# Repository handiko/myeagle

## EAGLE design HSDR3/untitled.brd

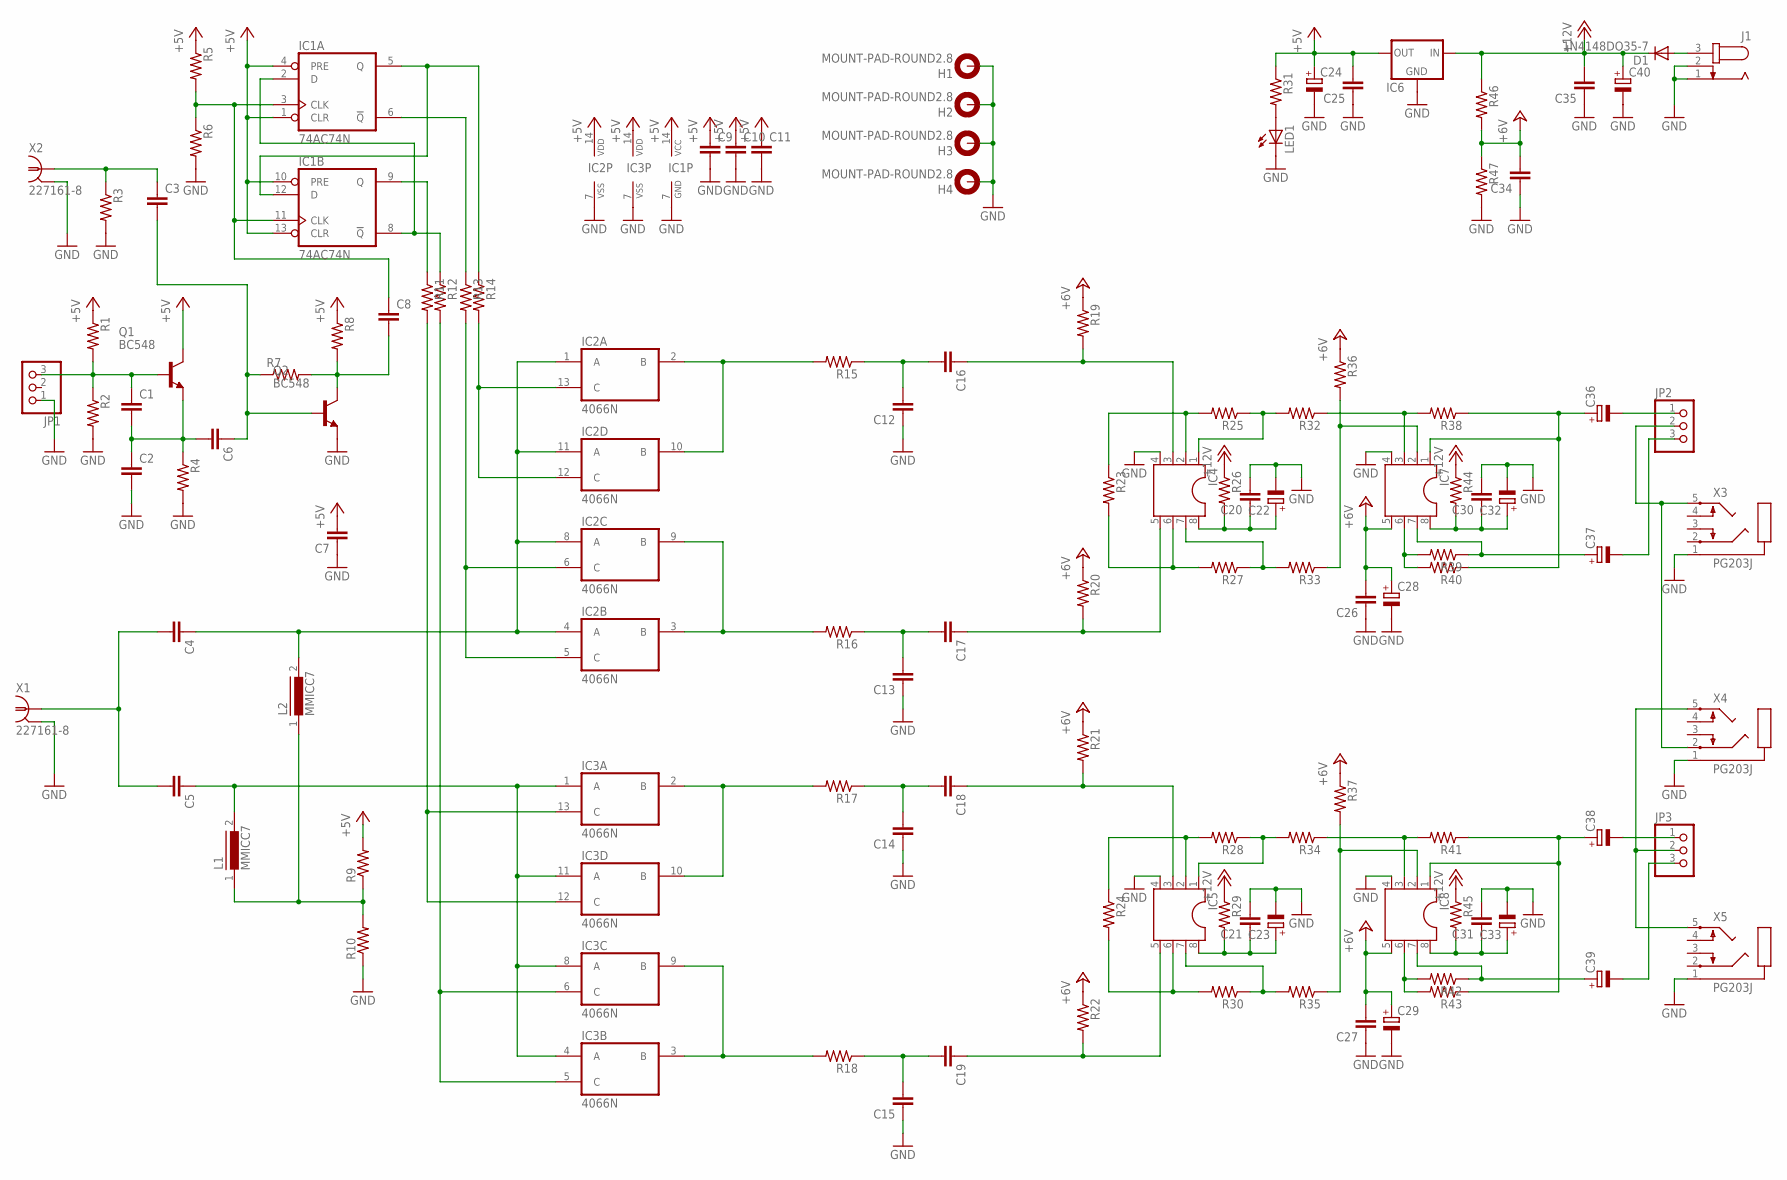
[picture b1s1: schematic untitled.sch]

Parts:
C1, C2: C-EU025-025X050; C025-025X050
C3, C4, C5, C6, C7, C9, C10, C11, C12, C13, C14, C15, C16, C17, C18, C19, C20, C21, C25, C26, C27, C30, C31, C34, C35: C-EU050-025X075; C050-025X075
C8: C-EU075-032X103; C075-032X103
C22, C23, C24, C28, C29, C32, C33, C36, C37, C38, C39, C40: CPOL-EUE5-6; E5-6
D1: 1N4148DO35-7; DO35-7
H1, H2, H3, H4: MOUNT-PAD-ROUND2.8; 2,8-PAD
IC1: 74AC74N; DIL14
IC2, IC3: 4066N; DIL14
IC4, IC5, IC7, IC8: DIL8; DIL08
IC6: 78XXS
J1: JACK-PLUG0; SPC4077
JP1, JP2, JP3: PINHD-1X3; 1X03
L1, L2: MMICC7
LED1: LED3MM
Q1, Q2: BC548; TO92-EBC
R1, R2, R3, R4, R5, R6, R7, R8, R9, R10, R11, R12, R13, R14, R15, R16, R17, R18, R19, R20, R21, R22, R23, R24, R25, R26, R27, R28, R29, R30, R31, R32, R33, R34, R35, R36, R37, R38, R39, R40, R41, R42, R43, R44, R45, R46, R47: R-US_0207/7; 0207/7
X1, X2: 227161-8; AMP_227161
X3, X4, X5: PG203J

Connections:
+5V: C7.2, C9.1, C10.1, C11.1, C24.+, C25.2, IC1.1 (CLR), IC1.4 (PRE), IC1.10 (PRE), IC1.13 (CLR), IC1.14 (VCC), IC2.14 (VDD), IC3.14 (VDD), IC6.OUT, Q1.C, R1.1, R5.1, R8.1, R9.2, R31.1
+12V: C35.2, C40.+, D1.C, IC6.IN, R26.1, R29.1, R44.1, R45.1, R46.1
+24V: C26.2, C27.2, C28.+, C29.+, C34.2, IC7.5, IC8.5, R19.1, R20.1, R21.1, R22.1, R36.1, R37.1, R46.2, R47.1
GND: C2.2, C7.1, C9.2, C10.2, C11.2, C12.1, C13.1, C14.1, C15.1, C20.2, C21.2, C22.-, C23.-, C24.-, C25.1, C26.1, C27.1, C28.-, C29.-, C30.2, C31.2, C32.-, C33.-, C34.1, C35.1, C40.-, H1.B2,8, H2.B2,8, H3.B2,8, H4.B2,8, IC1.7 (GND), IC2.7 (VSS), IC3.7 (VSS), IC4.4, IC5.4, IC6.GND, IC7.4, IC8.4, J1.1, J1.2, JP1.1, LED1.K (C), Q2.E, R2.2, R3.2, R4.2, R6.2, R10.1, R47.2, X1.2, X2.2, X3.1, X4.1, X5.1
unnamed: L1.1, L2.1, R9.1, R10.2
unnamed: C4.2, C5.2, X1.1
unnamed: C4.1, IC2.1 (A), IC2.4 (A), IC2.8 (A), IC2.11 (A), L2.2
unnamed: C5.1, IC3.1 (A), IC3.4 (A), IC3.8 (A), IC3.11 (A), L1.2
unnamed: IC2.3 (B), IC2.9 (B), R16.2
unnamed: IC2.2 (B), IC2.10 (B), R15.2
unnamed: IC3.2 (B), IC3.10 (B), R17.2
unnamed: IC3.3 (B), IC3.9 (B), R18.2
unnamed: IC2.12 (C), IC2.13 (C), R14.2
unnamed: IC2.5 (C), IC2.6 (C), R13.2
unnamed: IC3.12 (C), IC3.13 (C), R11.2
unnamed: IC3.5 (C), IC3.6 (C), R12.2
unnamed: C12.2, C16.2, R15.1
unnamed: C13.2, C17.2, R16.1
unnamed: C14.2, C18.2, R17.1
unnamed: C15.2, C19.2, R18.1
unnamed: IC1.2 (D), IC1.8 (!Q), R12.1
unnamed: IC1.6 (!Q), R13.1
unnamed: IC1.5 (Q), IC1.12 (D), R14.1
unnamed: IC1.9 (Q), R11.1
unnamed: C8.1, IC1.3 (CLK), IC1.11 (CLK), R5.2, R6.1
unnamed: C16.1, IC4.3, R19.2
unnamed: C17.1, IC4.5, R20.2
unnamed: IC4.2, R23.1, R25.2
unnamed: IC4.6, R23.2, R27.2
unnamed: IC4.7, R27.1, R33.2
unnamed: IC4.1, R25.1, R32.2
unnamed: IC7.2, R33.1, R36.2
unnamed: C36.+, IC7.1, R38.1, R40.1
unnamed: IC7.3, R32.1, R38.2
unnamed: IC7.6, R39.2, R40.2
unnamed: C37.+, IC7.7, R39.1
unnamed: C20.1, C22.+, IC4.8, R26.2
unnamed: C30.1, C32.+, IC7.8, R44.2
unnamed: D1.A, J1.3
unnamed: C3.1, R3.1, X2.1
unnamed: C36.-, JP2.1
unnamed: C18.1, IC5.3, R21.2
unnamed: C19.1, IC5.5, R22.2
unnamed: IC5.2, R24.1, R28.2
unnamed: IC5.6, R24.2, R30.2
unnamed: IC5.7, R30.1, R35.2
unnamed: IC5.1, R28.1, R34.2
unnamed: IC8.3, R34.1, R41.2
unnamed: IC8.2, R35.1, R37.2
unnamed: C38.+, IC8.1, R41.1, R43.1
unnamed: IC8.6, R42.2, R43.2
unnamed: C39.+, IC8.7, R42.1
unnamed: C21.1, C23.+, IC5.8, R29.2
unnamed: C31.1, C33.+, IC8.8, R45.2
unnamed: C37.-, JP2.3
unnamed: C38.-, JP3.1
unnamed: C39.-, JP3.3
unnamed: C1.1, JP1.3, Q1.B, R1.2, R2.1
unnamed: C1.2, C2.1, C6.2, Q1.E, R4.1
unnamed: JP2.2, X3.5, X4.2
unnamed: C8.2, Q2.C, R7.2, R8.2
unnamed: C3.2, C6.1, Q2.B, R7.1
unnamed: LED1.A, R31.2
unnamed: JP3.2, X4.5, X5.5

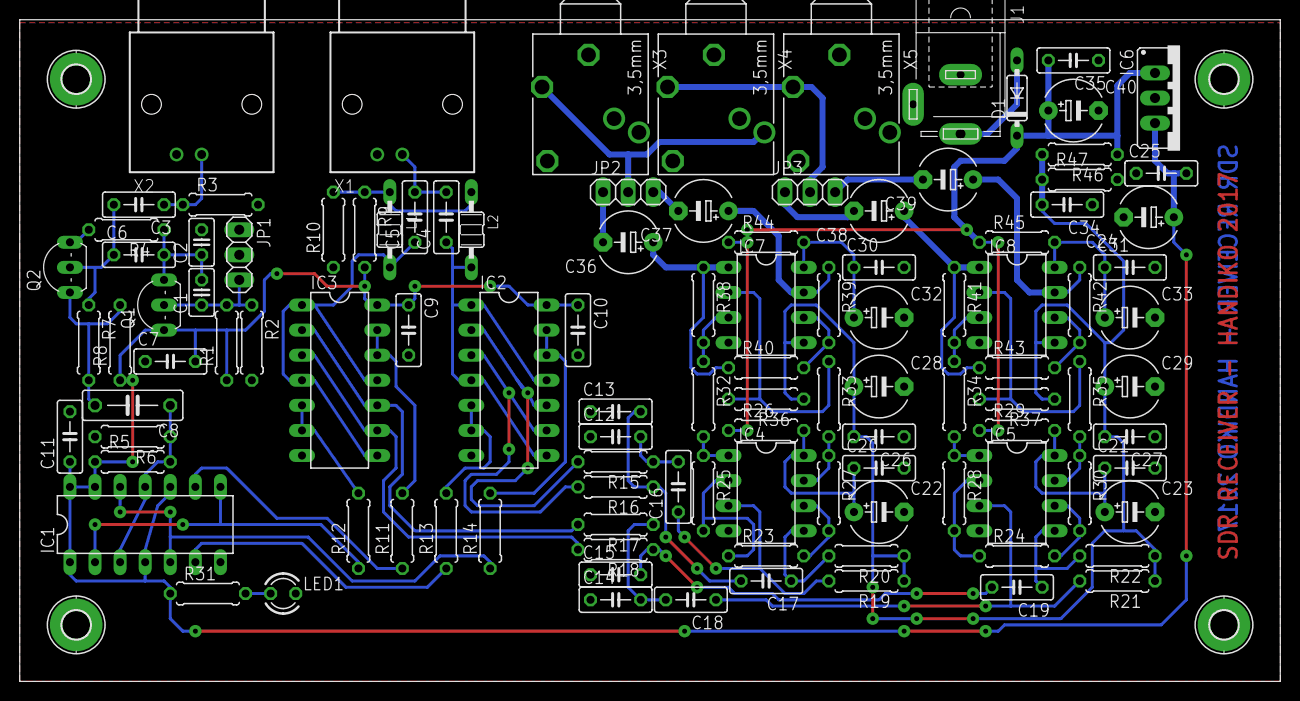
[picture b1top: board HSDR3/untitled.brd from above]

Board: 2 copper layers, 127.6 x 67.0 mm, 114 parts (0 on the bottom side), 64 nets.

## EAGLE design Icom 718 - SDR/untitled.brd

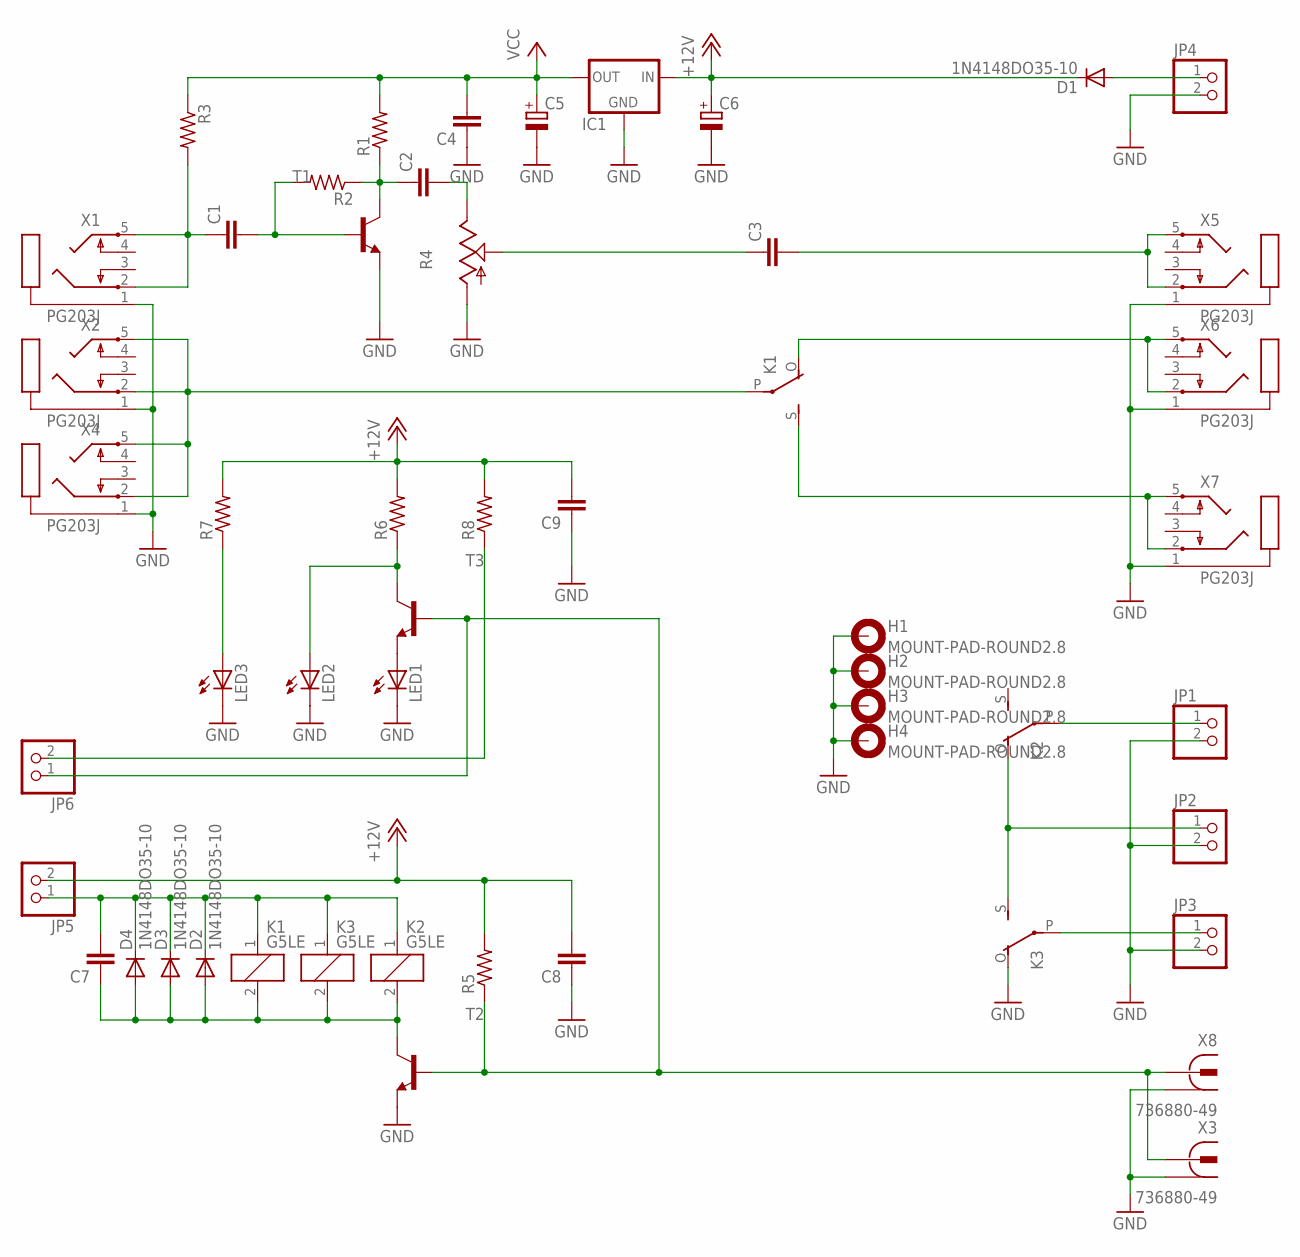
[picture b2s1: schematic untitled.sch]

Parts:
C1, C2, C3, C4, C7, C8, C9: C-EU050-025X075; C050-025X075
C5, C6: CPOL-EUE2.5-6; E2,5-6
D1, D2, D3, D4: 1N4148DO35-10; DO35-10
H1, H2, H3, H4: MOUNT-PAD-ROUND2.8; 2,8-PAD
IC1: 78XXS
JP1, JP2, JP3, JP4, JP5, JP6: PINHD-1X2; 1X02
K1, K2, K3: G5LE
LED1, LED2, LED3: LED3MM
R1, R2, R3, R5, R6, R7, R8: R-US_0207/7; 0207/7
R4: TRIM_US-CIP20C-6MM; CIP20C-6MM
T1, T2, T3: -NPN-TO92-EBC; TO92-EBC
X1, X2, X4, X5, X6, X7: PG203J
X3, X8: 736880-49

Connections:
+12V: C6.+, C8.2, C9.2, D1.C, IC1.IN, JP5.2, R5.2, R6.2, R7.2, R8.2
GND: C4.1, C5.-, C6.-, C8.1, C9.1, H1.B2,8, H2.B2,8, H3.B2,8, H4.B2,8, IC1.GND, JP1.2, JP2.2, JP3.2, JP4.2, K3.O, LED1.K (C), LED2.K (C), LED3.K (C), R4.A, T1.E, T2.E, X1.1, X2.1, X3.1, X3.1@1 (1), X3.1@2 (1), X4.1, X5.1, X6.1, X7.1, X8.1, X8.1@1 (1), X8.1@2 (1)
unnamed: C3.1, R4.S
unnamed: C1.1, R3.2, X1.2, X1.5
unnamed: C1.2, R2.2, T1.B
unnamed: C2.1, R1.1, R2.1, T1.C
unnamed: C2.2, R4.E
unnamed: JP6.1, R5.1, T2.B, T3.B, X3.2, X8.2
unnamed: C3.2, X5.2, X5.5
unnamed: K1.P, X2.2, X2.5, X4.2, X4.5
unnamed: K1.O, X6.2, X6.5
unnamed: K1.S, X7.2, X7.5
unnamed: JP3.1, K3.P
unnamed: JP1.1, K2.P
unnamed: JP2.1, K2.O, K3.S
unnamed: D1.A, JP4.1
unnamed: C7.1, D2.A, D3.A, D4.A, K1.2, K2.2, K3.2, T2.C
unnamed: JP6.2, R8.1
unnamed: C7.2, D2.C, D3.C, D4.C, JP5.1, K1.1, K2.1, K3.1
unnamed: LED1.A, T3.E
unnamed: LED2.A, R6.1, T3.C
unnamed: LED3.A, R7.1
VCC: C4.2, C5.+, IC1.OUT, R1.2, R3.1

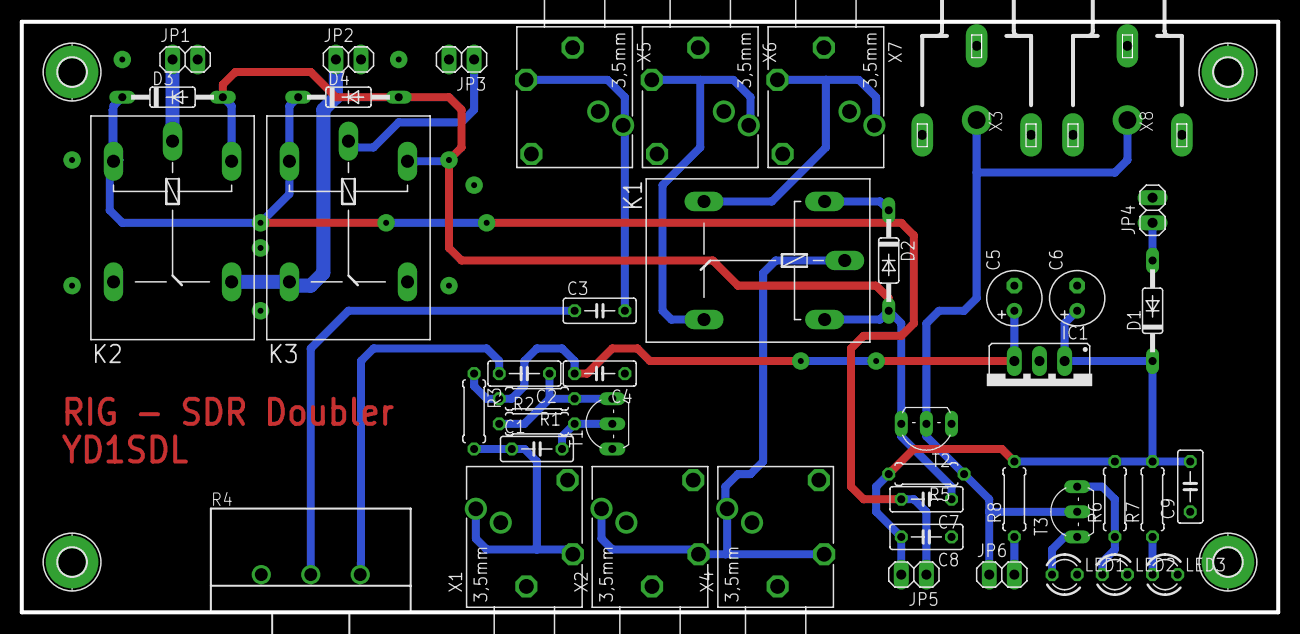
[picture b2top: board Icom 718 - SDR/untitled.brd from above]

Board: 2 copper layers, 127.0 x 59.7 mm, 49 parts (0 on the bottom side), 23 nets.

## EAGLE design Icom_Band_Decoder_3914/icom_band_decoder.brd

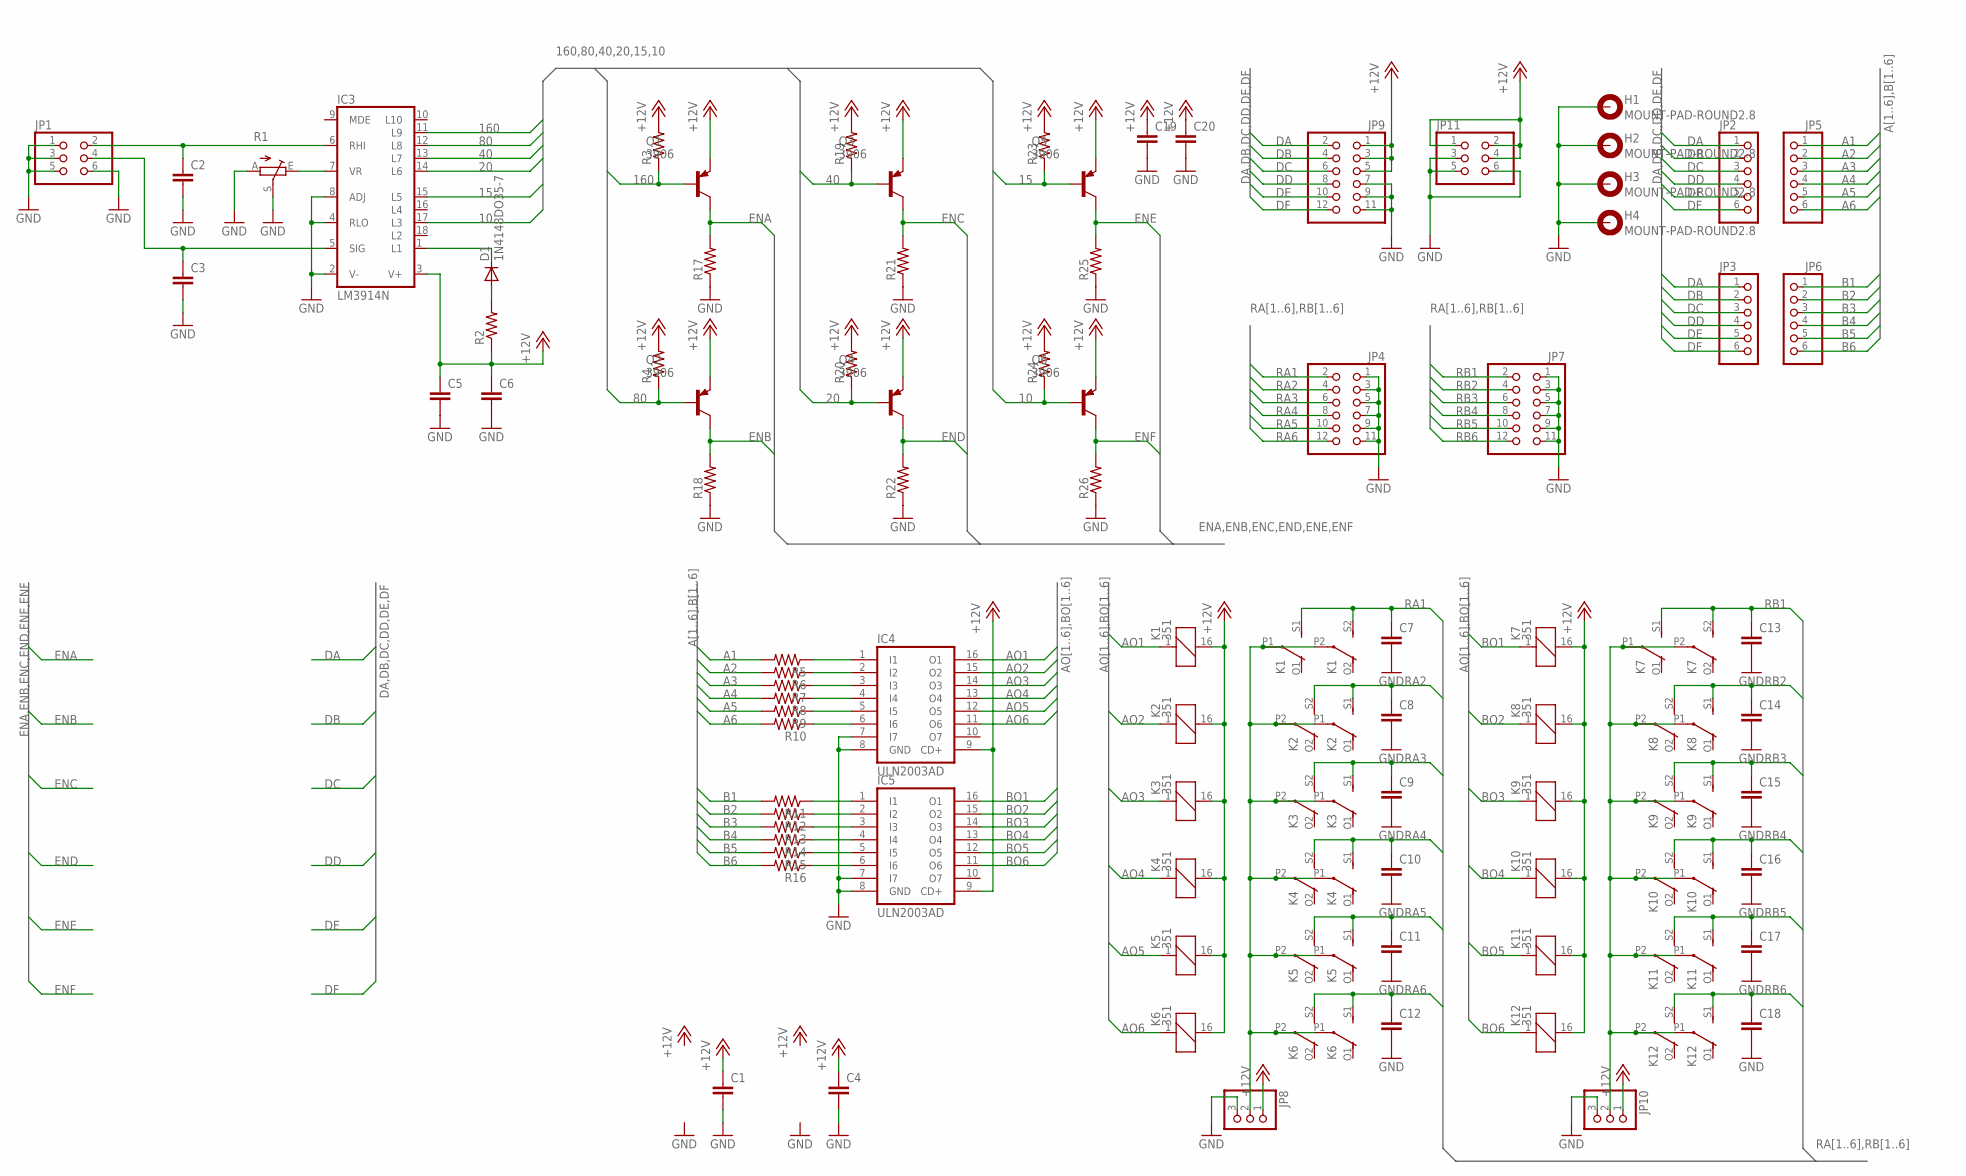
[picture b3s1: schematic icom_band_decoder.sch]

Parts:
C1, C4, C6, C7, C8, C9, C10, C11, C12, C13, C14, C15, C16, C17, C18, C19, C20: C-EU050-024X044; C050-024X044
C2, C3, C5: C-EUC0805K; C0805K
D1: 1N4148DO35-7; DO35-7
H1, H2, H3, H4: MOUNT-PAD-ROUND2.8; 2,8-PAD
IC3: LM3914N; DIL18
IC4, IC5: ULN2003AD; SO16
JP1, JP11: PINHD-2X3; 2X03
JP2, JP3, JP5, JP6: PINHD-1X6; 1X06
JP4, JP7, JP9: PINHD-2X6; 2X06
JP8, JP10: PINHD-1X3; 1X03
K1, K2, K3, K4, K5, K6, K7, K8, K9, K10, K11, K12: 351
Q1, Q2, Q3, Q4, Q5, Q6: 3906; SOT23-BEC
R1: TRIM_EU-CA6V; CA6V
R2, R3, R4, R5, R6, R7, R8, R9, R10, R11, R12, R13, R14, R15, R16, R17, R18, R19, R20, R21, R22, R23, R24, R25, R26: R-US_M0805; M0805

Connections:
10: IC3.17 (L3), Q6.B, R24.1
15: IC3.15 (L5), Q5.B, R23.1
20: IC3.14 (L6), Q4.B, R20.1
40: IC3.13 (L7), Q3.B, R19.1
80: IC3.12 (L8), Q2.B, R4.1
160: IC3.11 (L9), Q1.B, R3.1
+12V: C1.1, C4.1, C5.1, C6.1, C19.1, C20.1, IC3.3 (V+), IC4.9 (CD+), IC5.9 (CD+), JP8.1, JP9.1, JP9.3, JP9.5, JP10.1, JP11.1, JP11.2, JP11.4, K1.16 (2), K2.16 (2), K3.16 (2), K4.16 (2), K5.16 (2), K6.16 (2), K7.16 (2), K8.16 (2), K9.16 (2), K10.16 (2), K11.16 (2), K12.16 (2), Q1.E, Q2.E, Q3.E, Q4.E, Q5.E, Q6.E, R2.1, R3.2, R4.2, R19.2, R20.2, R23.2, R24.2
A1: JP5.1, R5.2
A2: JP5.2, R6.2
A3: JP5.3, R7.2
A4: JP5.4, R8.2
A5: JP5.5, R9.2
A6: JP5.6, R10.2
AO1: IC4.16 (O1), K1.1
AO2: IC4.15 (O2), K2.1
AO3: IC4.14 (O3), K3.1
AO4: IC4.13 (O4), K4.1
AO5: IC4.12 (O5), K5.1
AO6: IC4.11 (O6), K6.1
B1: JP6.1, R11.2
B2: JP6.2, R12.2
B3: JP6.3, R13.2
B4: JP6.4, R14.2
B5: JP6.5, R15.2
B6: JP6.6, R16.2
BO1: IC5.16 (O1), K7.1
BO2: IC5.15 (O2), K8.1
BO3: IC5.14 (O3), K9.1
BO4: IC5.13 (O4), K10.1
BO5: IC5.12 (O5), K11.1
BO6: IC5.11 (O6), K12.1
DA: JP2.1, JP3.1, JP9.2
DB: JP2.2, JP3.2, JP9.4
DC: JP2.3, JP3.3, JP9.6
DD: JP2.4, JP3.4, JP9.8
DE: JP2.5, JP3.5, JP9.10
DF: JP2.6, JP3.6, JP9.12
ENA: Q1.C, R17.2
ENB: Q2.C, R18.2
ENC: Q3.C, R21.2
END: Q4.C, R22.2
ENE: Q5.C, R25.2
ENF: Q6.C, R26.2
GND: C1.2, C2.2, C3.2, C4.2, C5.2, C6.2, C7.2, C8.2, C9.2, C10.2, C11.2, C12.2, C13.2, C14.2, C15.2, C16.2, C17.2, C18.2, C19.2, C20.2, H1.B2,8, H2.B2,8, H3.B2,8, H4.B2,8, IC3.2 (V-), IC3.4 (RLO), IC3.8 (ADJ), IC4.7 (I7), IC4.8 (GND), IC5.7 (I7), IC5.8 (GND), JP1.1, JP1.3, JP1.5, JP1.6, JP4.1, JP4.3, JP4.5, JP4.7, JP4.9, JP4.11, JP7.1, JP7.3, JP7.5, JP7.7, JP7.9, JP7.11, JP8.3, JP9.7, JP9.9, JP9.11, JP10.3, JP11.3, JP11.5, JP11.6, R1.A, R1.S, R17.1, R18.1, R21.1, R22.1, R25.1, R26.1
unnamed: C2.1, IC3.6 (RHI), JP1.2
unnamed: C3.1, IC3.5 (SIG), JP1.4
unnamed: IC3.7 (VR), R1.E
unnamed: D1.C, IC3.1 (L1)
unnamed: D1.A, R2.2
unnamed: IC4.1 (I1), R5.1
unnamed: IC4.2 (I2), R6.1
unnamed: IC4.3 (I3), R7.1
unnamed: IC4.4 (I4), R8.1
unnamed: IC4.5 (I5), R9.1
unnamed: IC4.6 (I6), R10.1
unnamed: IC5.1 (I1), R11.1
unnamed: JP8.2, K1.P1, K1.P2, K2.P1, K2.P2, K3.P1, K3.P2, K4.P1, K4.P2, K5.P1, K5.P2, K6.P1, K6.P2
unnamed: IC5.2 (I2), R12.1
unnamed: IC5.3 (I3), R13.1
unnamed: IC5.4 (I4), R14.1
unnamed: IC5.5 (I5), R15.1
unnamed: IC5.6 (I6), R16.1
unnamed: JP10.2, K7.P1, K7.P2, K8.P1, K8.P2, K9.P1, K9.P2, K10.P1, K10.P2, K11.P1, K11.P2, K12.P1, K12.P2
RA1: C7.1, JP4.2, K1.S1 (S), K1.S2 (S)
RA2: C8.1, JP4.4, K2.S1 (S), K2.S2 (S)
RA3: C9.1, JP4.6, K3.S1 (S), K3.S2 (S)
RA4: C10.1, JP4.8, K4.S1 (S), K4.S2 (S)
RA5: C11.1, JP4.10, K5.S1 (S), K5.S2 (S)
RA6: C12.1, JP4.12, K6.S1 (S), K6.S2 (S)
RB1: C13.1, JP7.2, K7.S1 (S), K7.S2 (S)
RB2: C14.1, JP7.4, K8.S1 (S), K8.S2 (S)
RB3: C15.1, JP7.6, K9.S1 (S), K9.S2 (S)
RB4: C16.1, JP7.8, K10.S1 (S), K10.S2 (S)
RB5: C17.1, JP7.10, K11.S1 (S), K11.S2 (S)
RB6: C18.1, JP7.12, K12.S1 (S), K12.S2 (S)

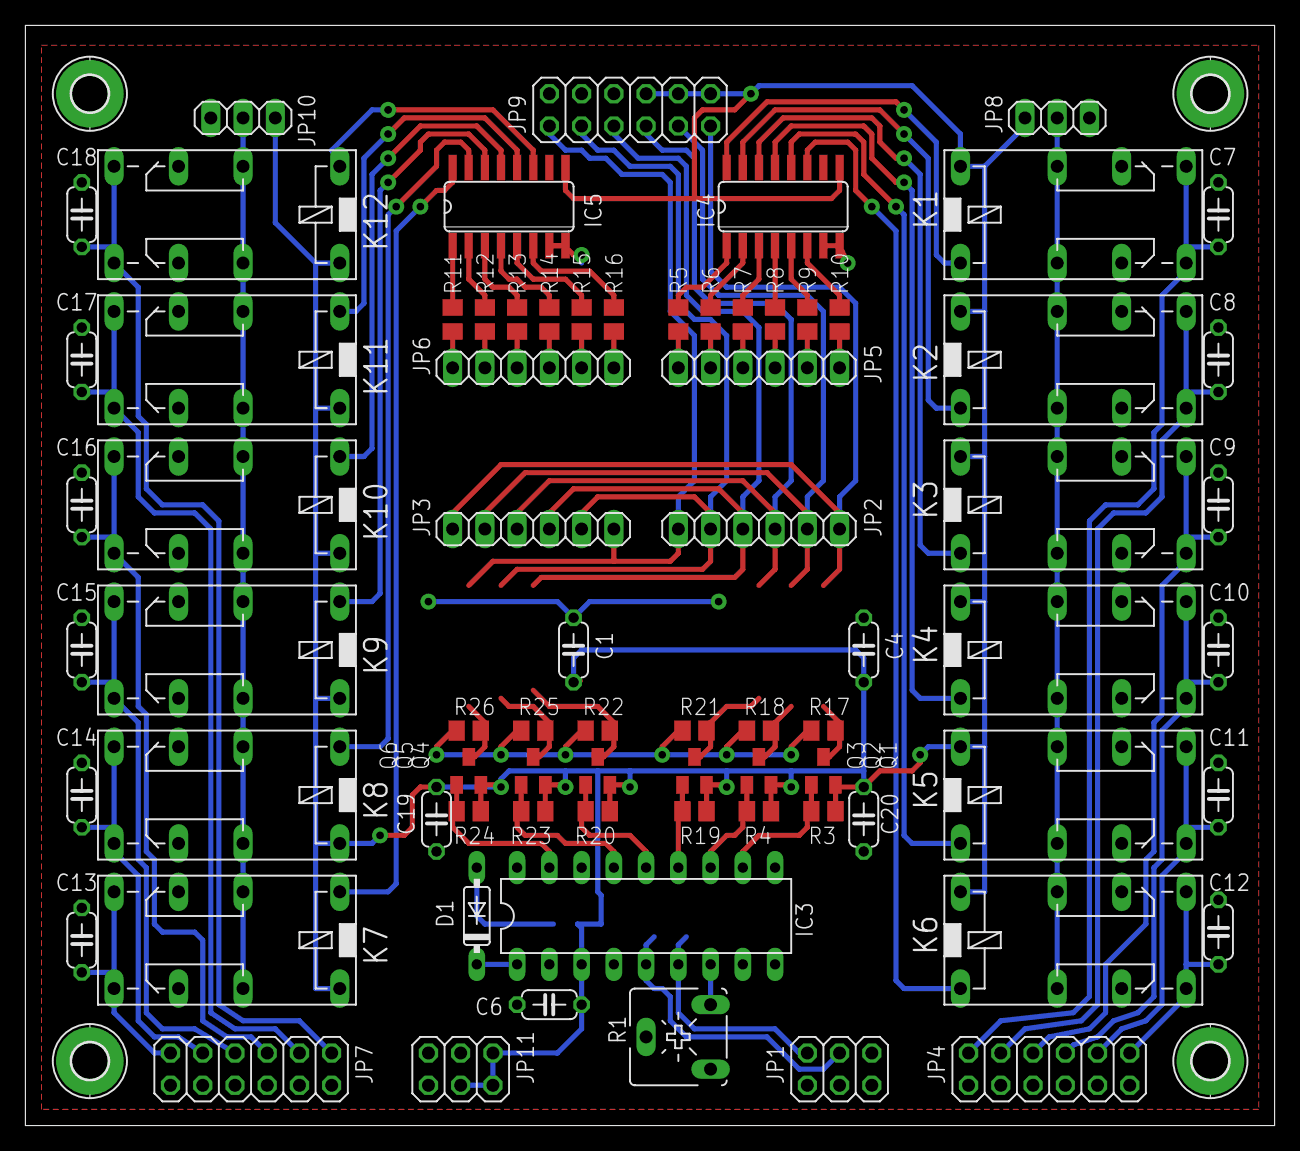
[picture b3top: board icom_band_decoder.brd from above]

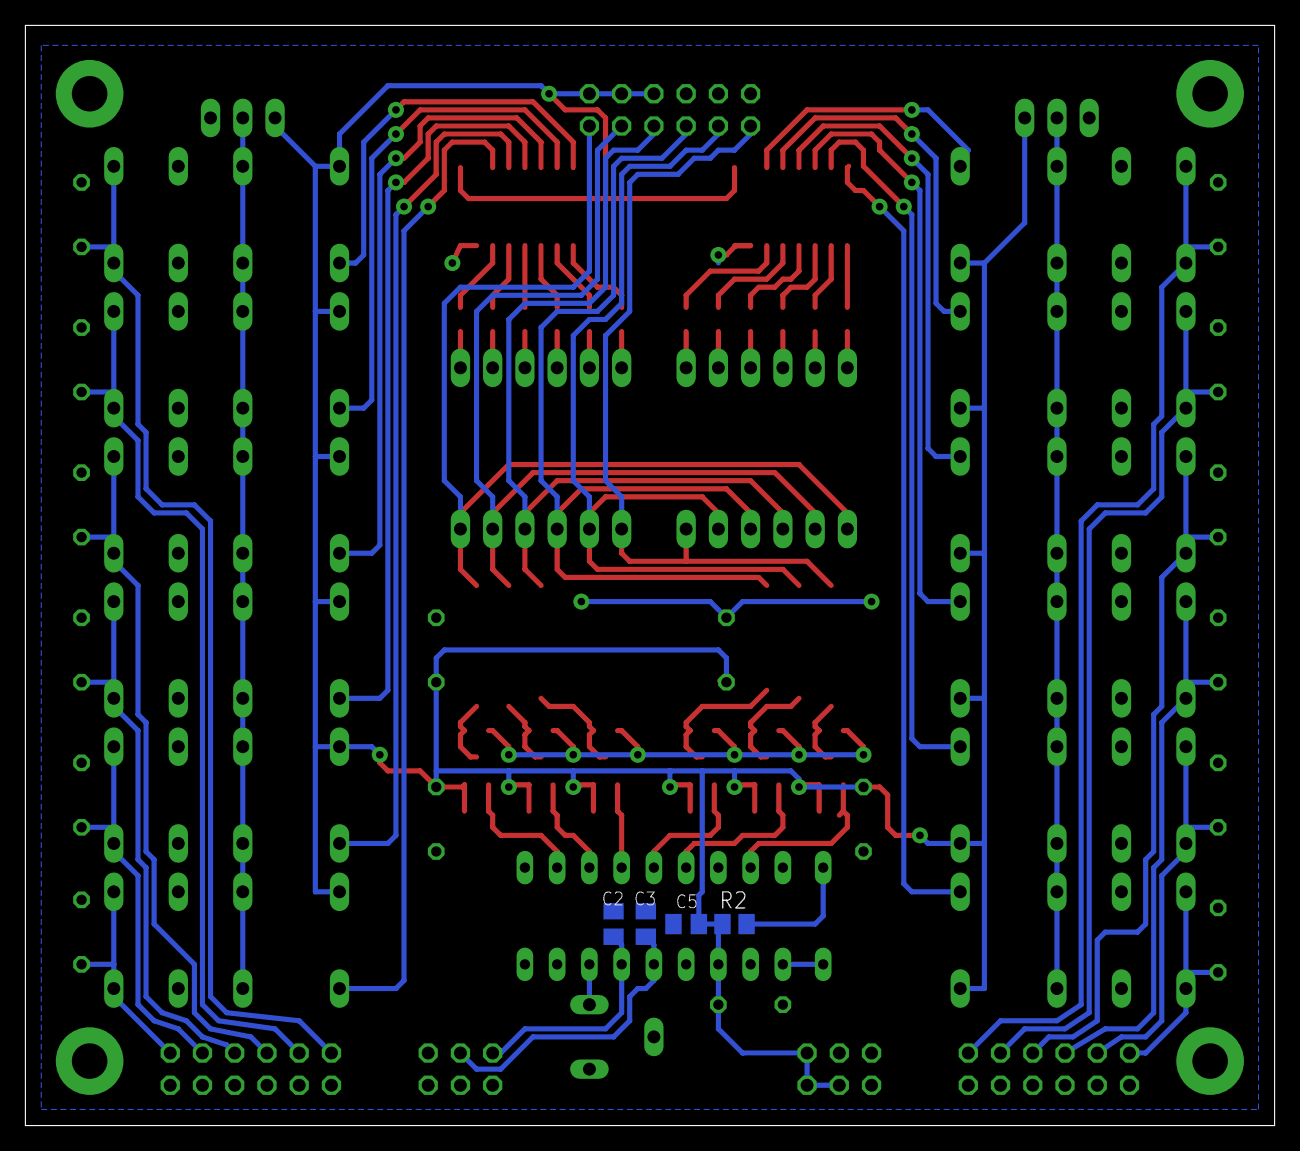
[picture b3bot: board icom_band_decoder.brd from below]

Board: 2 copper layers, 98.4 x 86.7 mm, 83 parts (4 on the bottom side), 75 nets.

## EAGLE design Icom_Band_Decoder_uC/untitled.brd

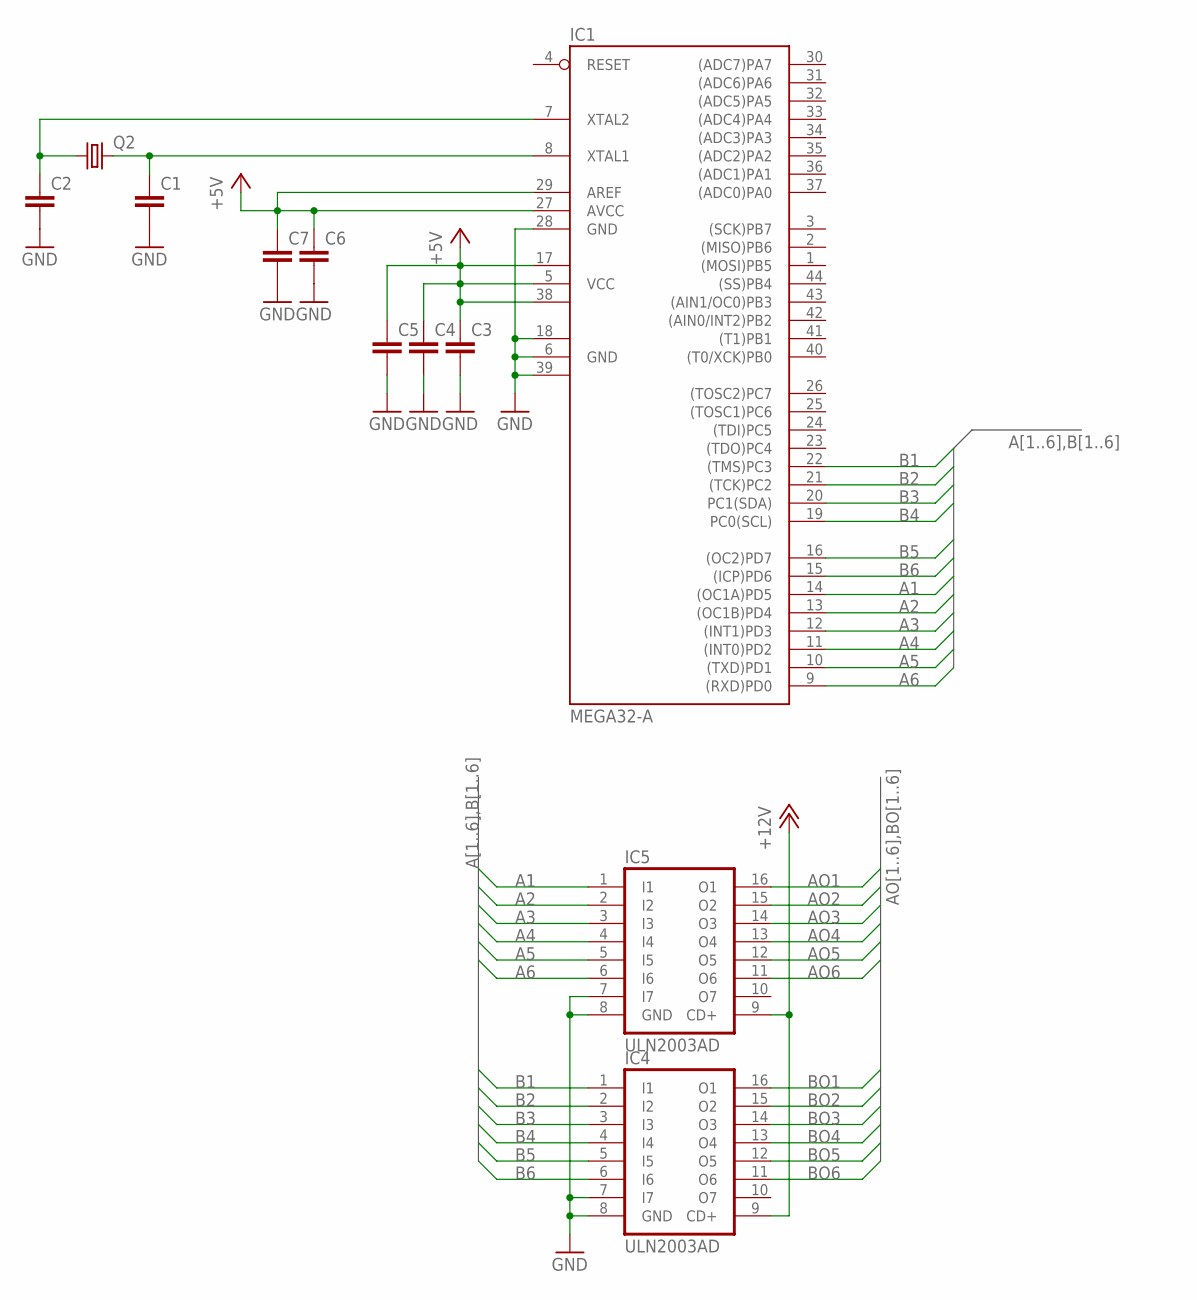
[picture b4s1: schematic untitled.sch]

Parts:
C1, C2, C3, C4, C5, C6, C7: C-EUC0805K; C0805K
IC1: MEGA32-A; TQFP44
IC4, IC5: ULN2003AD; SO16
Q2: CRYSTALSM49; SM49

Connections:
+5V: C3.1, C4.1, C5.1, C6.1, C7.1, IC1.5 (VCC), IC1.17 (VCC1), IC1.27 (AVCC), IC1.29 (AREF), IC1.38 (VCC2)
+12V: IC4.9 (CD+), IC5.9 (CD+)
A1: IC1.14 ((OC1A)PD5), IC5.1 (I1)
A2: IC1.13 ((OC1B)PD4), IC5.2 (I2)
A3: IC1.12 ((INT1)PD3), IC5.3 (I3)
A4: IC1.11 ((INT0)PD2), IC5.4 (I4)
A5: IC1.10 ((TXD)PD1), IC5.5 (I5)
A6: IC1.9 ((RXD)PD0), IC5.6 (I6)
AO1: IC5.16 (O1)
AO2: IC5.15 (O2)
AO3: IC5.14 (O3)
AO4: IC5.13 (O4)
AO5: IC5.12 (O5)
AO6: IC5.11 (O6)
B1: IC1.22 ((TMS)PC3), IC4.1 (I1)
B2: IC1.21 ((TCK)PC2), IC4.2 (I2)
B3: IC1.20 (PC1(SDA)), IC4.3 (I3)
B4: IC1.19 (PC0(SCL)), IC4.4 (I4)
B5: IC1.16 ((OC2)PD7), IC4.5 (I5)
B6: IC1.15 ((ICP)PD6), IC4.6 (I6)
BO1: IC4.16 (O1)
BO2: IC4.15 (O2)
BO3: IC4.14 (O3)
BO4: IC4.13 (O4)
BO5: IC4.12 (O5)
BO6: IC4.11 (O6)
GND: C1.2, C2.2, C3.2, C4.2, C5.2, C6.2, C7.2, IC1.6 (GND), IC1.18 (GND1), IC1.28 (GND), IC1.39 (GND2), IC4.7 (I7), IC4.8 (GND), IC5.7 (I7), IC5.8 (GND)
unnamed: C2.1, IC1.7 (XTAL2), Q2.1
unnamed: C1.1, IC1.8 (XTAL1), Q2.2

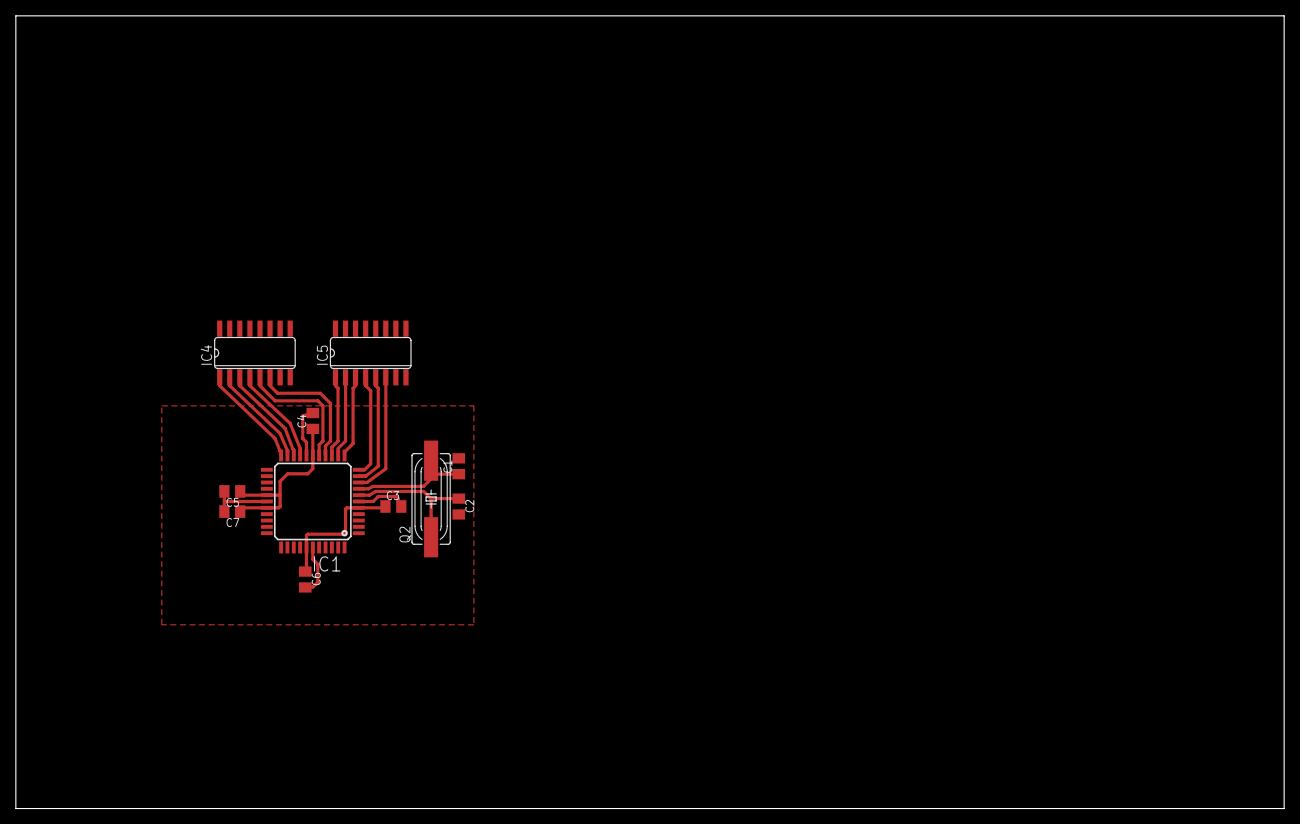
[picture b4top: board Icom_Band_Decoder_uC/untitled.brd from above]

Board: 2 copper layers, 160.0 x 100.0 mm, 11 parts (0 on the bottom side), 17 nets.

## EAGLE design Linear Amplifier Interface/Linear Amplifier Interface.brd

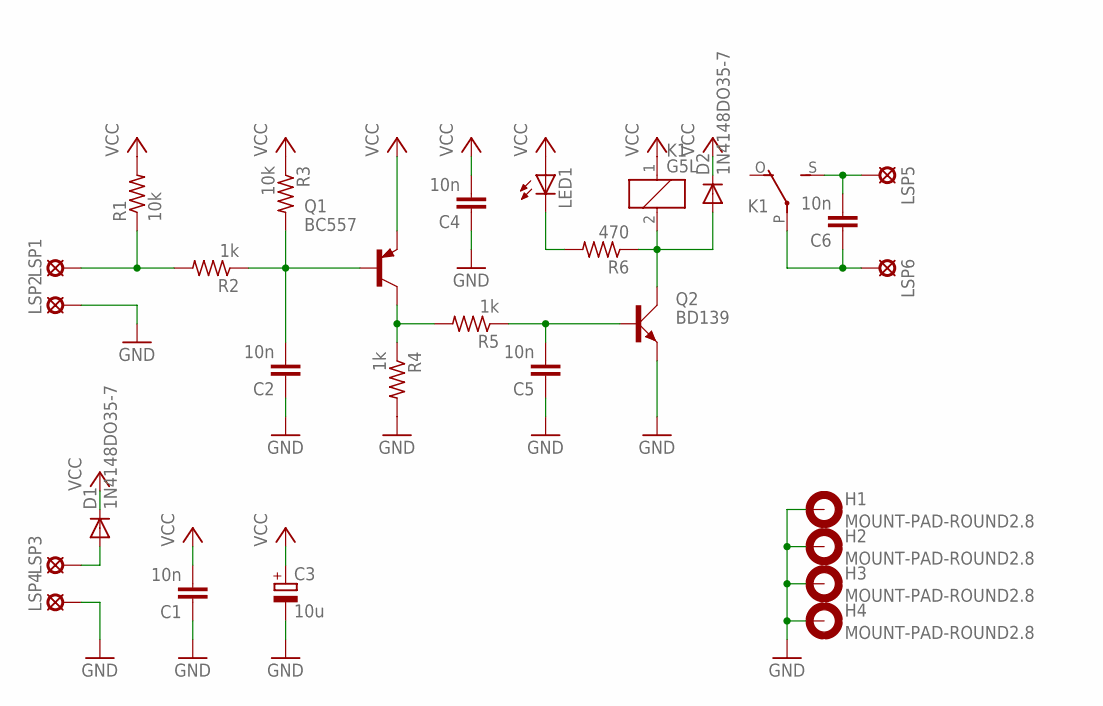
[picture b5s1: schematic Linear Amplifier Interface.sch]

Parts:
C1, C2, C4, C5, C6: 10n; C1206K
C3: 10u; E5-6
D1, D2: 1N4148DO35-7; DO35-7
H1, H2, H3, H4: MOUNT-PAD-ROUND2.8; 2,8-PAD
K1: G5L; G5LE
LED1: LED3MM
LSP1, LSP2, LSP3, LSP4, LSP5, LSP6: SE11
Q1: BC557; TO92-EBC
Q2: BD139; TO126AV
R1, R3: 10k; M1206
R2, R4, R5: 1k; M1206
R6: 470; M1206

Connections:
GND: C1.1, C2.1, C3.-, C4.1, C5.1, H1.B2,8, H2.B2,8, H3.B2,8, H4.B2,8, LSP2.MP, LSP4.MP, Q2.E, R4.2
unnamed: C5.2, Q2.B, R5.1
unnamed: C2.2, Q1.B, R2.1, R3.2
unnamed: Q1.C, R4.1, R5.2
unnamed: LSP1.MP, R1.1, R2.2
unnamed: LED1.K (C), R6.2
unnamed: D2.A, K1.2, Q2.C, R6.1
unnamed: D1.A, LSP3.MP
unnamed: C6.2, K1.S, LSP5.MP
unnamed: C6.1, K1.P, LSP6.MP
VCC: C1.2, C3.+, C4.2, D1.C, D2.C, K1.1, LED1.A, Q1.E, R1.2, R3.1

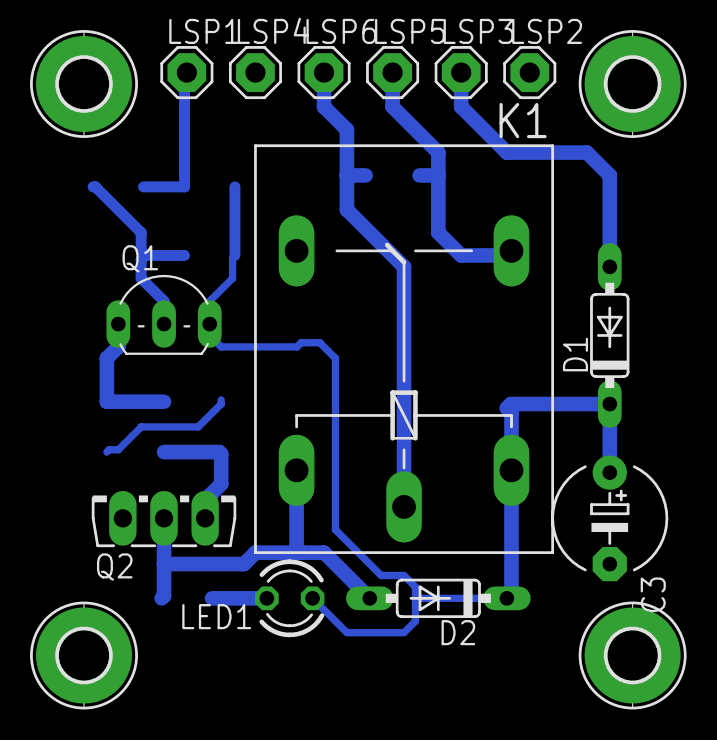
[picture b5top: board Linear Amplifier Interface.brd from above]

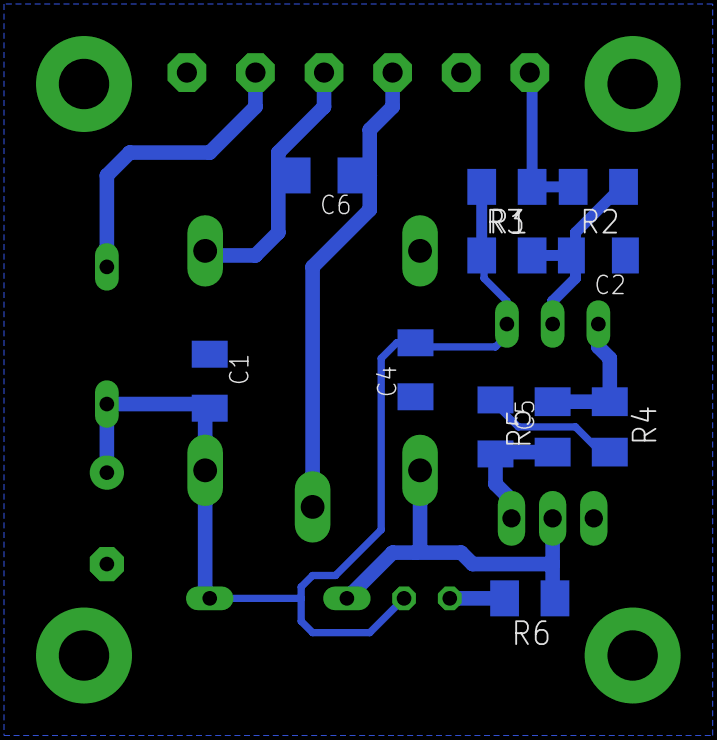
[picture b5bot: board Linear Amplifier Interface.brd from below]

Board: 2 copper layers, 28 parts (11 on the bottom side), 11 nets.
